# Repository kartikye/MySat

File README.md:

# SASSat
Singapore American School Satellite

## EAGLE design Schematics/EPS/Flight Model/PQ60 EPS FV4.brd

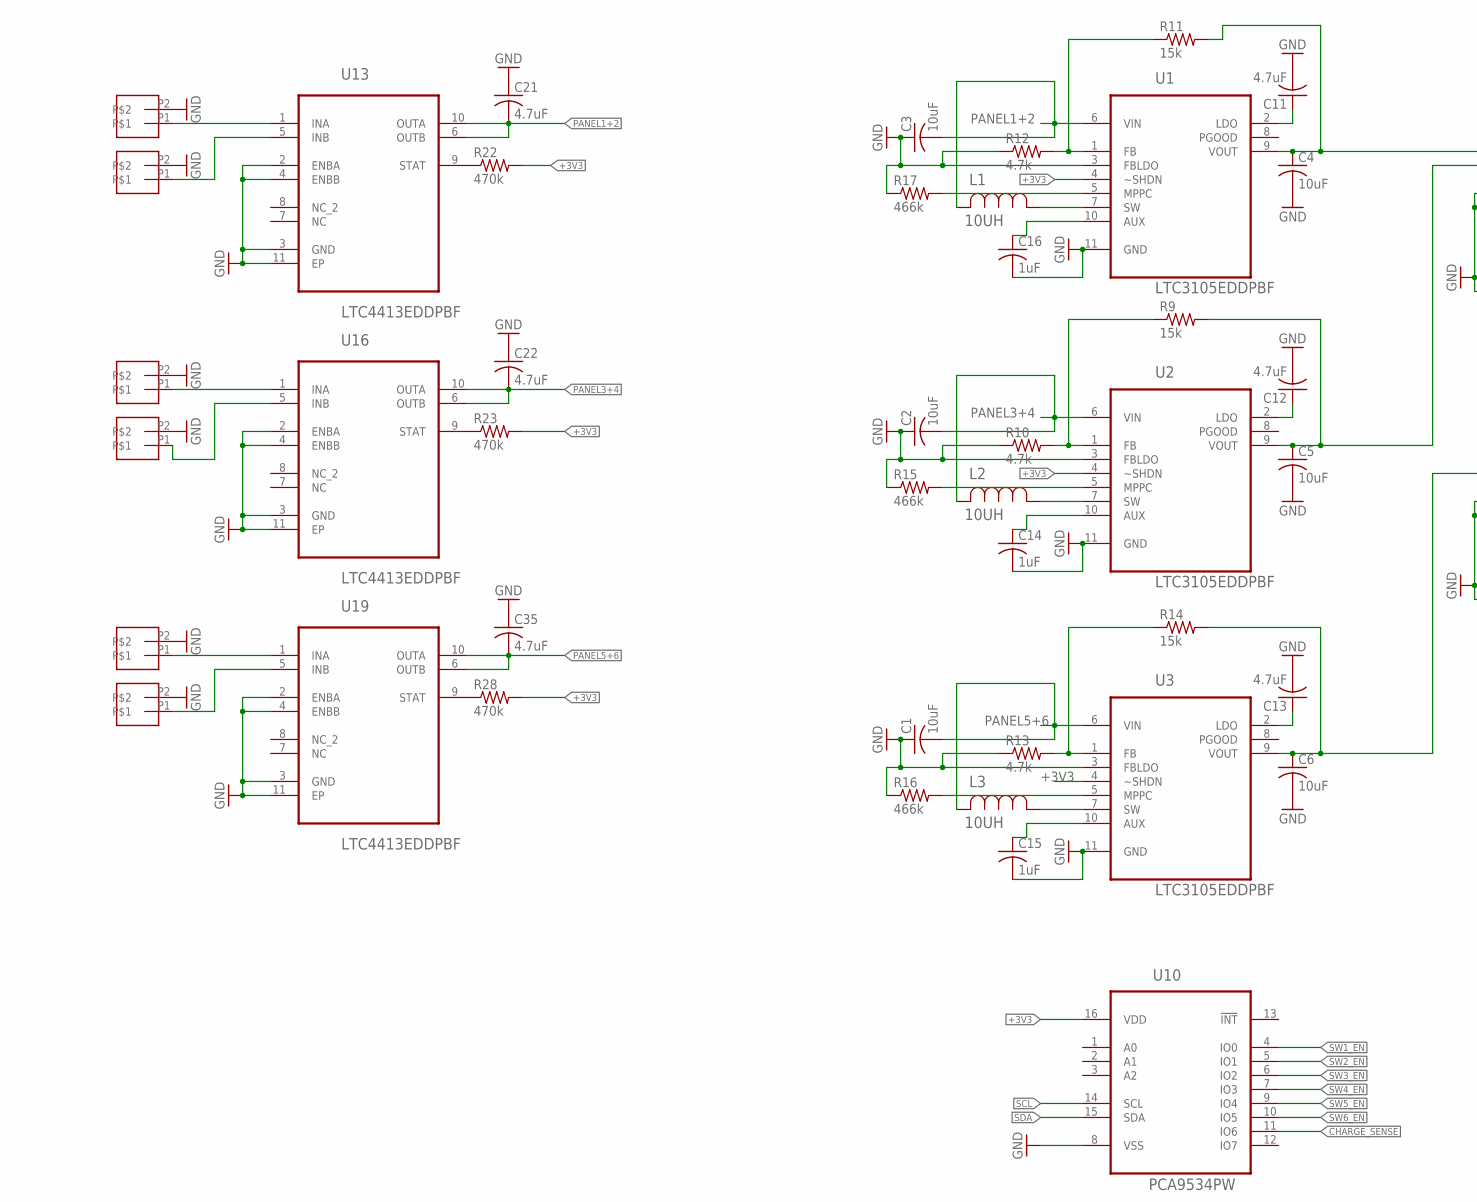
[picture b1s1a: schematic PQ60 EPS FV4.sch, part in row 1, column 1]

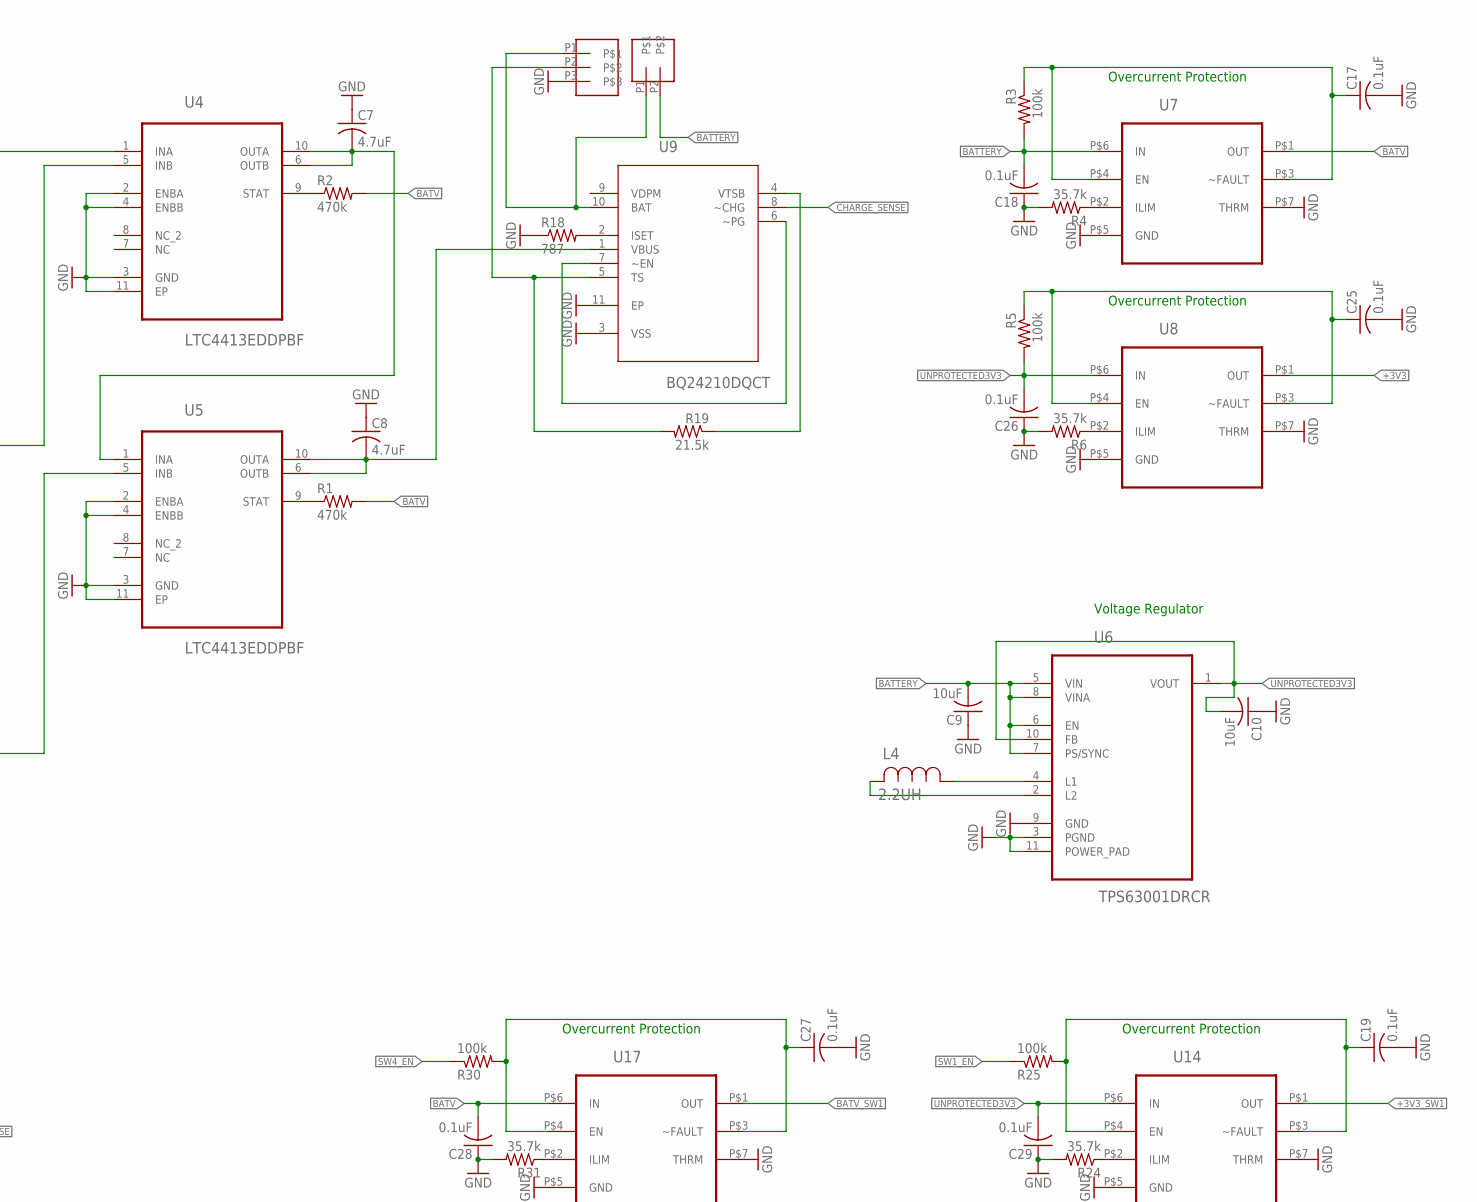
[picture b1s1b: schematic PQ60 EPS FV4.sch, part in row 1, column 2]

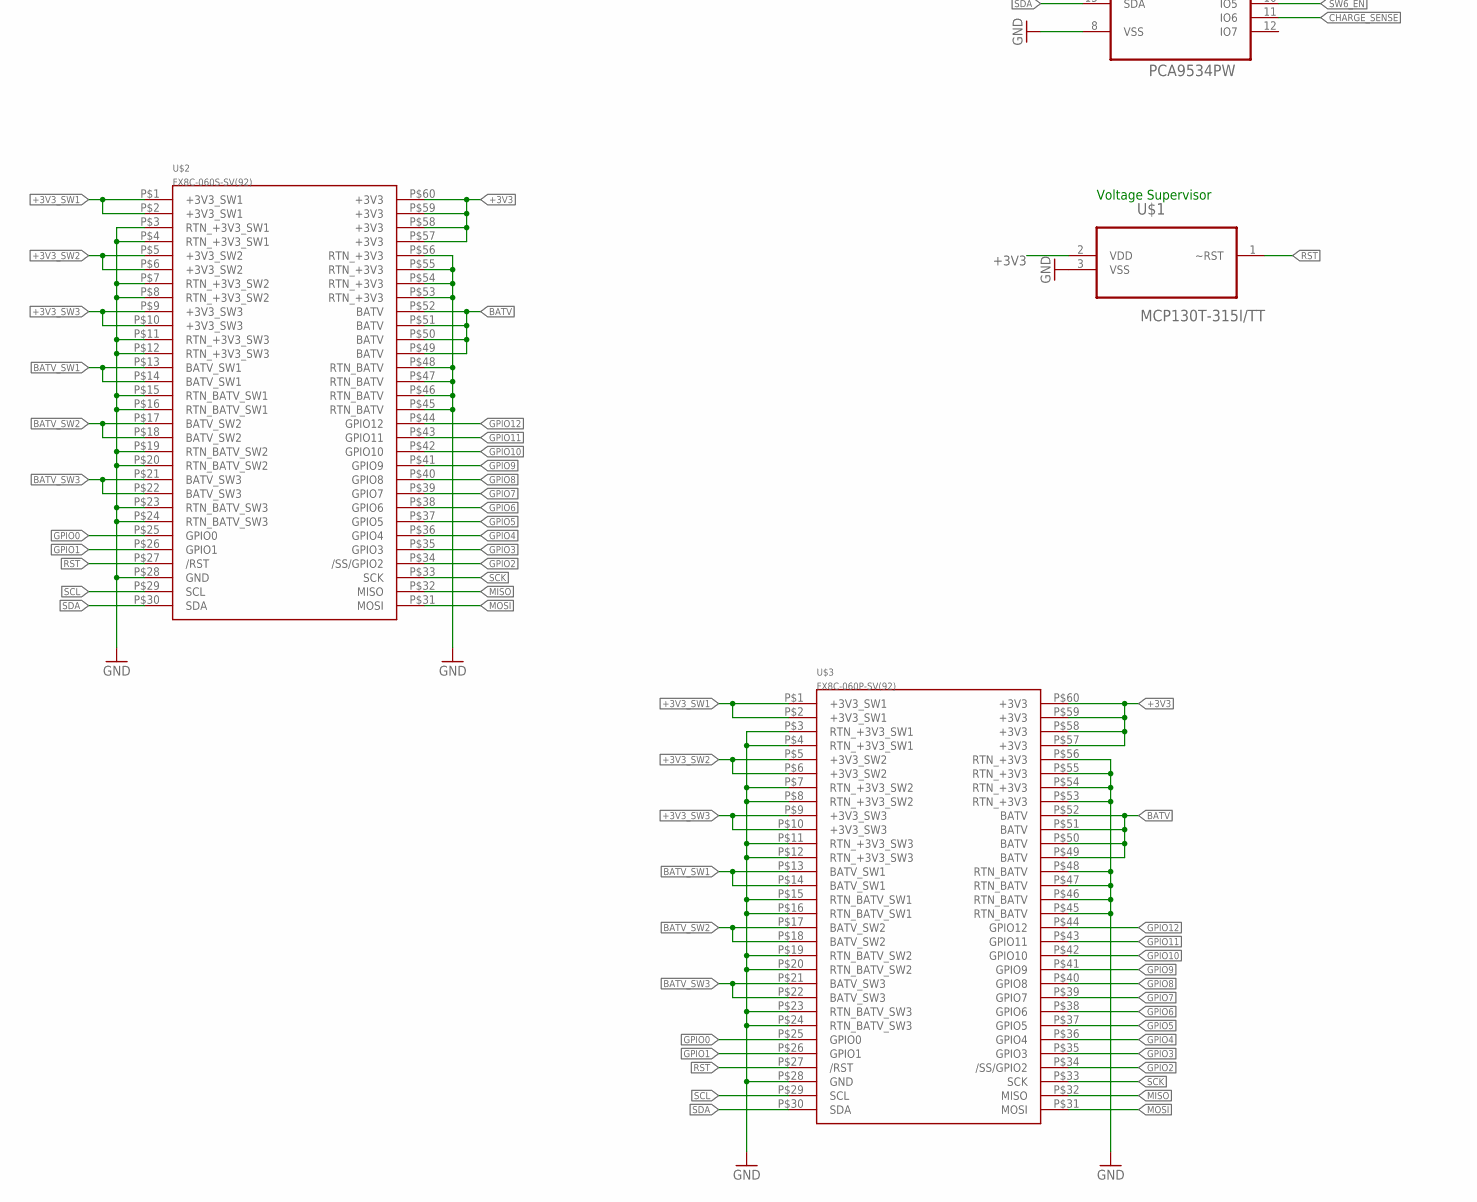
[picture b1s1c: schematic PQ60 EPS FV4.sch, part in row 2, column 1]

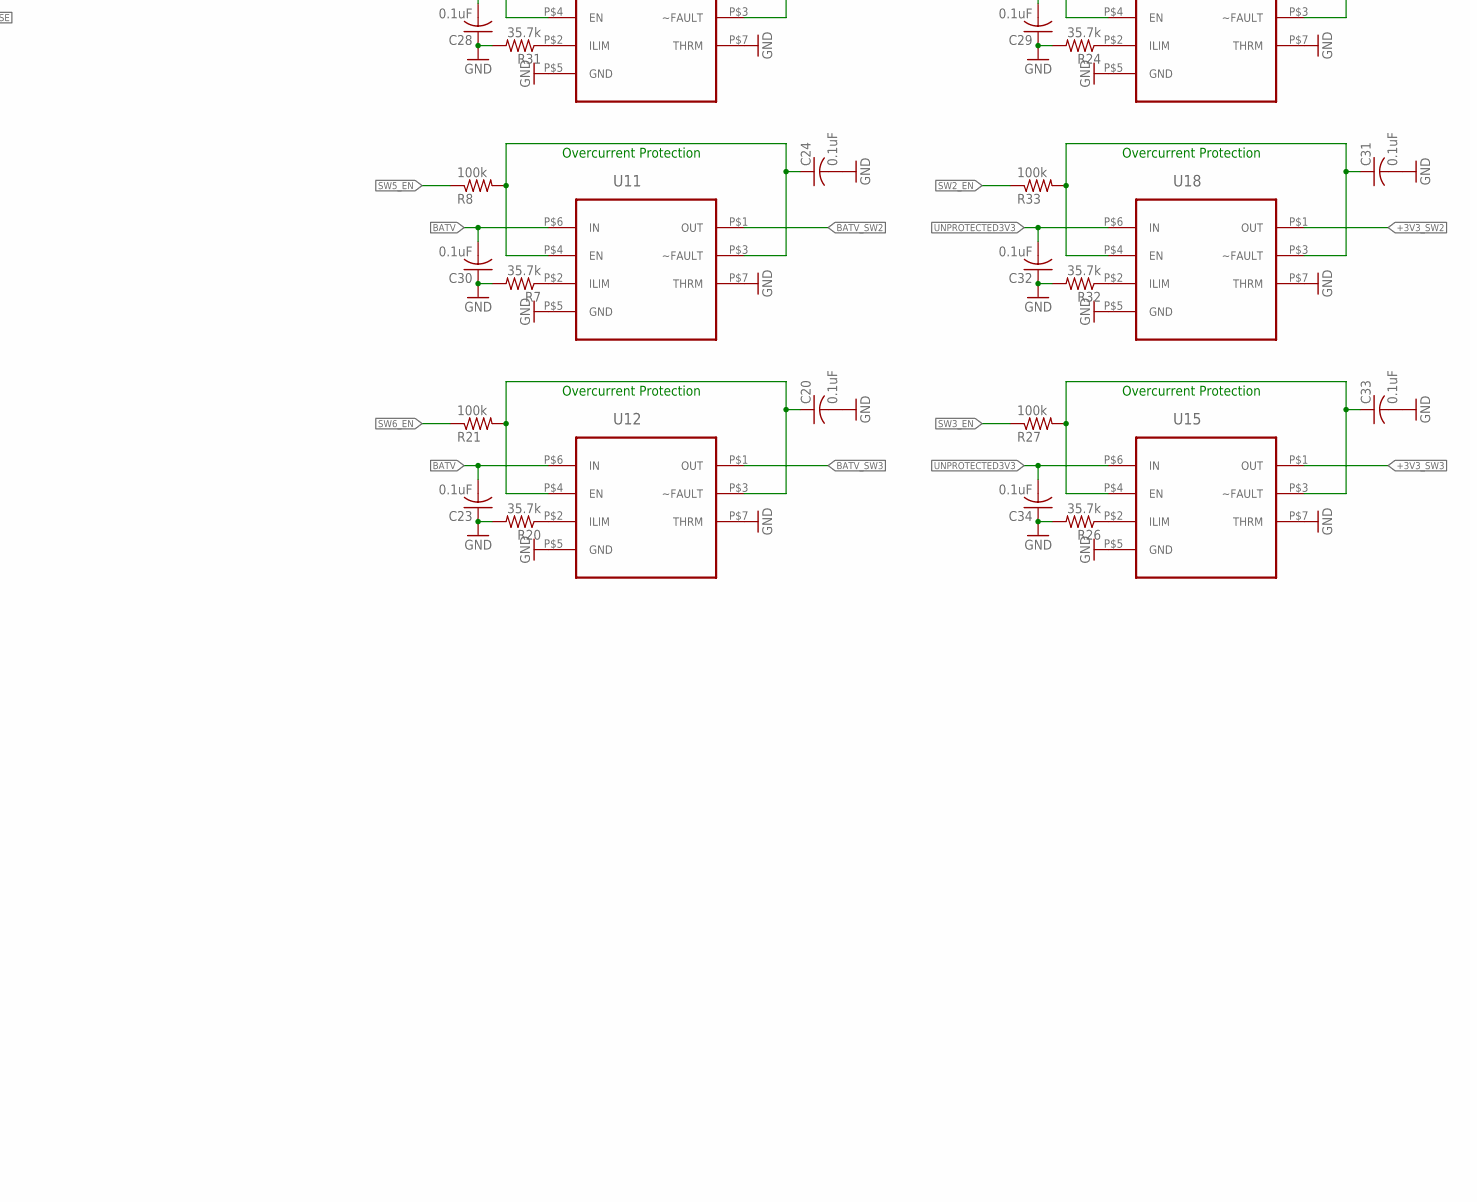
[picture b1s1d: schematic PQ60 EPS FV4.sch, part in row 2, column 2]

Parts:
C1, C2, C3, C4, C5, C6, C9, C10: 10uF; C0805
C7, C8, C11, C12, C13, C21, C22, C35: 4.7uF; C0805
C14, C15, C16: 1uF; C0805
C17, C18, C19, C20, C23, C24, C25, C26, C27, C28, C29, C30, C31, C32, C33, C34: 0.1uF; C0805
L1, L2, L3: 10UH; IND_ELL6XH
L4: 2.2UH; IND_ELL3FU
R1, R2, R22, R23, R28: 470k; R0805
R3, R5, R8, R21, R25, R27, R30, R33: 100k; R0805
R4, R6, R7, R20, R24, R26, R31, R32: 35.7k; R0805
R9, R11, R14: 15k; R0805
R10, R12, R13: 4.7k; R0805
R15, R16, R17: 466k; R0805
R18: 787; R0805
R19: 21.5k; R0805
U1, U2, U3: LTC3105EDDPBF; DFN300X300X80-11N
U4, U5, U13, U16, U19: LTC4413EDDPBF; DFN300X300X80-11N
U6: TPS63001DRCR; SON50P300X300X100-11N
U7, U8, U11, U12, U14, U15, U17, U18: DRV
U9: BQ24210DQCT; SON50P200X300X80-11N
U10: PCA9534PW; SOP65P640X110-16N
U$1: MCP130T-315I/TT; SOT95P237X112-3N
U$2: FX8C-060S-SV(92)
U$3: FX8C-060P-SV(92)
U$4, U$5, U$6, U$7, U$8, U$9, U$10: JST-SH-02
U$11: JST-SH-03

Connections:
!RST: U$1.1 (~RST), U$2.P$27 (/RST), U$3.P$27 (/RST)
+3V3: R22.2, R23.2, R28.2, U1.4 (~SHDN), U2.4 (~SHDN), U3.4 (~SHDN), U8.P$1 (OUT), U10.16 (VDD), U$1.2 (VDD), U$2.P$57 (+3V3), U$2.P$58 (+3V3), U$2.P$59 (+3V3), U$2.P$60 (+3V3), U$3.P$57 (+3V3), U$3.P$58 (+3V3), U$3.P$59 (+3V3), U$3.P$60 (+3V3)
+3V3_SW1: U14.P$1 (OUT), U$2.P$1 (+3V3_SW1), U$2.P$2 (+3V3_SW1), U$3.P$1 (+3V3_SW1), U$3.P$2 (+3V3_SW1)
+3V3_SW2: U18.P$1 (OUT), U$2.P$5 (+3V3_SW2), U$2.P$6 (+3V3_SW2), U$3.P$5 (+3V3_SW2), U$3.P$6 (+3V3_SW2)
+3V3_SW3: U15.P$1 (OUT), U$2.P$9 (+3V3_SW3), U$2.P$10 (+3V3_SW3), U$3.P$9 (+3V3_SW3), U$3.P$10 (+3V3_SW3)
BATTERY: C9.2, C18.2, R3.2, U6.5 (VIN), U6.6 (EN), U6.7 (PS/SYNC), U6.8 (VINA), U7.P$6 (IN), U$10.P2
BATV: C23.2, C28.2, C30.2, R1.2, R2.2, U7.P$1 (OUT), U11.P$6 (IN), U12.P$6 (IN), U17.P$6 (IN), U$2.P$49 (BATV), U$2.P$50 (BATV), U$2.P$51 (BATV), U$2.P$52 (BATV), U$3.P$49 (BATV), U$3.P$50 (BATV), U$3.P$51 (BATV), U$3.P$52 (BATV)
BATV_SW1: U17.P$1 (OUT), U$2.P$13 (BATV_SW1), U$2.P$14 (BATV_SW1), U$3.P$13 (BATV_SW1), U$3.P$14 (BATV_SW1)
BATV_SW2: U11.P$1 (OUT), U$2.P$17 (BATV_SW2), U$2.P$18 (BATV_SW2), U$3.P$17 (BATV_SW2), U$3.P$18 (BATV_SW2)
BATV_SW3: U12.P$1 (OUT), U$2.P$21 (BATV_SW3), U$2.P$22 (BATV_SW3), U$3.P$21 (BATV_SW3), U$3.P$22 (BATV_SW3)
CHARGE_SENSE: U9.8 (~CHG), U10.11 (IO6)
GND: C1.1, C2.1, C3.1, C4.2, C5.2, C6.2, C7.1, C8.1, C9.1, C10.1, C11.2, C12.2, C13.2, C14.2, C15.2, C16.2, C17.2, C18.1, C19.2, C20.2, C21.1, C22.1, C23.1, C24.2, C25.2, C26.1, C27.2, C28.1, C29.1, C30.1, C31.2, C32.1, C33.2, C34.1, C35.1, R4.2, R6.2, R7.2, R10.1, R12.1, R13.1, R15.1, R16.1, R17.1, R18.1, R20.2, R24.2, R26.2, R31.2, R32.2, U1.3 (FBLDO), U1.11 (GND), U2.3 (FBLDO), U2.11 (GND), U3.3 (FBLDO), U3.11 (GND), U4.2 (ENBA), U4.3 (GND), U4.4 (ENBB), U4.11 (EP), U5.2 (ENBA), U5.3 (GND), U5.4 (ENBB), U5.11 (EP), U6.3 (PGND), U6.9 (GND), U6.11 (POWER_PAD), U7.P$5 (GND), U7.P$7 (THRM), U8.P$5 (GND), U8.P$7 (THRM), U9.3 (VSS), U9.11 (EP), U10.8 (VSS), U11.P$5 (GND), U11.P$7 (THRM), U12.P$5 (GND), U12.P$7 (THRM), U13.2 (ENBA), U13.3 (GND), U13.4 (ENBB), U13.11 (EP), U14.P$5 (GND), U14.P$7 (THRM), U15.P$5 (GND), U15.P$7 (THRM), U16.2 (ENBA), U16.3 (GND), U16.4 (ENBB), U16.11 (EP), U17.P$5 (GND), U17.P$7 (THRM), U18.P$5 (GND), U18.P$7 (THRM), U19.2 (ENBA), U19.3 (GND), U19.4 (ENBB), U19.11 (EP), U$1.3 (VSS), U$2.P$3 (RTN_+3V3_SW1), U$2.P$4 (RTN_+3V3_SW1), U$2.P$7 (RTN_+3V3_SW2), U$2.P$8 (RTN_+3V3_SW2), U$2.P$11 (RTN_+3V3_SW3), U$2.P$12 (RTN_+3V3_SW3), U$2.P$15 (RTN_BATV_SW1), U$2.P$16 (RTN_BATV_SW1), U$2.P$19 (RTN_BATV_SW2), U$2.P$20 (RTN_BATV_SW2), U$2.P$23 (RTN_BATV_SW3), U$2.P$24 (RTN_BATV_SW3), U$2.P$28 (GND), U$2.P$45 (RTN_BATV), U$2.P$46 (RTN_BATV), U$2.P$47 (RTN_BATV), U$2.P$48 (RTN_BATV), U$2.P$53 (RTN_+3V3), U$2.P$54 (RTN_+3V3), U$2.P$55 (RTN_+3V3), U$2.P$56 (RTN_+3V3), U$3.P$3 (RTN_+3V3_SW1), U$3.P$4 (RTN_+3V3_SW1), U$3.P$7 (RTN_+3V3_SW2), U$3.P$8 (RTN_+3V3_SW2), U$3.P$11 (RTN_+3V3_SW3), U$3.P$12 (RTN_+3V3_SW3), U$3.P$15 (RTN_BATV_SW1), U$3.P$16 (RTN_BATV_SW1), U$3.P$19 (RTN_BATV_SW2), U$3.P$20 (RTN_BATV_SW2), U$3.P$23 (RTN_BATV_SW3), U$3.P$24 (RTN_BATV_SW3), U$3.P$28 (GND), U$3.P$45 (RTN_BATV), U$3.P$46 (RTN_BATV), U$3.P$47 (RTN_BATV), U$3.P$48 (RTN_BATV), U$3.P$53 (RTN_+3V3), U$3.P$54 (RTN_+3V3), U$3.P$55 (RTN_+3V3), U$3.P$56 (RTN_+3V3), U$4.P2, U$5.P2, U$6.P2, U$7.P2, U$8.P2, U$9.P2, U$11.P3
GPIO0: U$2.P$25 (GPIO0), U$3.P$25 (GPIO0)
GPIO1: U$2.P$26 (GPIO1), U$3.P$26 (GPIO1)
GPIO2: U$2.P$34 (/SS/GPIO2), U$3.P$34 (/SS/GPIO2)
GPIO3: U$2.P$35 (GPIO3), U$3.P$35 (GPIO3)
GPIO4: U$2.P$36 (GPIO4), U$3.P$36 (GPIO4)
GPIO5: U$2.P$37 (GPIO5), U$3.P$37 (GPIO5)
GPIO6: U$2.P$38 (GPIO6), U$3.P$38 (GPIO6)
GPIO7: U$2.P$39 (GPIO7), U$3.P$39 (GPIO7)
GPIO8: U$2.P$40 (GPIO8), U$3.P$40 (GPIO8)
GPIO9: U$2.P$41 (GPIO9), U$3.P$41 (GPIO9)
GPIO10: U$2.P$42 (GPIO10), U$3.P$42 (GPIO10)
GPIO11: U$2.P$43 (GPIO11), U$3.P$43 (GPIO11)
GPIO12: U$2.P$44 (GPIO12), U$3.P$44 (GPIO12)
MISO: U$2.P$32 (MISO), U$3.P$32 (MISO)
MOSI: U$2.P$31 (MOSI), U$3.P$31 (MOSI)
unnamed: L2.1, U2.7 (SW)
unnamed: L3.1, U3.7 (SW)
unnamed: L1.1, U1.7 (SW)
unnamed: L4.1, U6.4 (L1)
unnamed: C4.1, R11.2, U1.9 (VOUT), U4.1 (INA)
unnamed: C5.1, R9.2, U2.9 (VOUT), U4.5 (INB)
unnamed: C6.1, R14.2, U3.9 (VOUT), U5.5 (INB)
unnamed: C17.1, R3.1, U7.P$3 (~FAULT), U7.P$4 (EN)
unnamed: C7.2, U4.6 (OUTB), U4.10 (OUTA), U5.1 (INA)
unnamed: R1.1, U5.9 (STAT)
unnamed: R2.1, U4.9 (STAT)
unnamed: L4.2, U6.2 (L2)
unnamed: R4.1, U7.P$2 (ILIM)
unnamed: R6.1, U8.P$2 (ILIM)
unnamed: C25.1, R5.1, U8.P$3 (~FAULT), U8.P$4 (EN)
unnamed: R7.1, U11.P$2 (ILIM)
unnamed: C24.1, R8.2, U11.P$3 (~FAULT), U11.P$4 (EN)
unnamed: R13.2, R14.1, U3.1 (FB)
unnamed: C11.1, U1.2 (LDO)
unnamed: C12.1, U2.2 (LDO)
unnamed: C13.1, U3.2 (LDO)
unnamed: C14.1, U2.10 (AUX)
unnamed: C15.1, U3.10 (AUX)
unnamed: C16.1, U1.10 (AUX)
unnamed: R11.1, R12.2, U1.1 (FB)
unnamed: R9.1, R10.2, U2.1 (FB)
unnamed: R31.1, U17.P$2 (ILIM)
unnamed: R15.2, U2.5 (MPPC)
unnamed: R16.2, U3.5 (MPPC)
unnamed: R17.2, U1.5 (MPPC)
unnamed: C8.2, U5.6 (OUTB), U5.10 (OUTA), U9.1 (VBUS)
unnamed: U9.6 (~PG), U9.7 (~EN)
unnamed: R18.2, U9.2 (ISET)
unnamed: U9.10 (BAT), U$10.P1, U$11.P1
unnamed: R19.2, U9.5 (TS), U$11.P2
unnamed: R19.1, U9.4 (VTSB)
unnamed: C27.1, R30.2, U17.P$3 (~FAULT), U17.P$4 (EN)
unnamed: R20.1, U12.P$2 (ILIM)
unnamed: C20.1, R21.2, U12.P$3 (~FAULT), U12.P$4 (EN)
unnamed: R23.1, U16.9 (STAT)
unnamed: R28.1, U19.9 (STAT)
unnamed: R24.1, U14.P$2 (ILIM)
unnamed: C19.1, R25.2, U14.P$3 (~FAULT), U14.P$4 (EN)
unnamed: R26.1, U15.P$2 (ILIM)
unnamed: C33.1, R27.2, U15.P$3 (~FAULT), U15.P$4 (EN)
unnamed: U13.1 (INA), U$5.P1
unnamed: U13.5 (INB), U$4.P1
unnamed: R32.1, U18.P$2 (ILIM)
unnamed: C31.1, R33.2, U18.P$3 (~FAULT), U18.P$4 (EN)
unnamed: U16.1 (INA), U$6.P1
unnamed: U16.5 (INB), U$7.P1
unnamed: U19.1 (INA), U$9.P1
unnamed: U19.5 (INB), U$8.P1
unnamed: R22.1, U13.9 (STAT)
PANEL1+2: C3.2, C21.2, L1.2, U1.6 (VIN), U13.6 (OUTB), U13.10 (OUTA)
PANEL3+4: C2.2, C22.2, L2.2, U2.6 (VIN), U16.6 (OUTB), U16.10 (OUTA)
PANEL5+6: C1.2, C35.2, L3.2, U3.6 (VIN), U19.6 (OUTB), U19.10 (OUTA)
SCK: U$2.P$33 (SCK), U$3.P$33 (SCK)
SCL: U10.14 (SCL), U$2.P$29 (SCL), U$3.P$29 (SCL)
SDA: U10.15 (SDA), U$2.P$30 (SDA), U$3.P$30 (SDA)
SW1_EN: R25.1, U10.4 (IO0)
SW2_EN: R33.1, U10.5 (IO1)
SW3_EN: R27.1, U10.6 (IO2)
SW4_EN: R30.1, U10.7 (IO3)
SW5_EN: R8.1, U10.9 (IO4)
SW6_EN: R21.1, U10.10 (IO5)
UNPROTECTED3V3: C10.2, C26.2, C29.2, C32.2, C34.2, R5.2, U6.1 (VOUT), U6.10 (FB), U8.P$6 (IN), U14.P$6 (IN), U15.P$6 (IN), U18.P$6 (IN)

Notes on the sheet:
Voltage Regulator
Voltage Supervisor
Overcurrent Protection

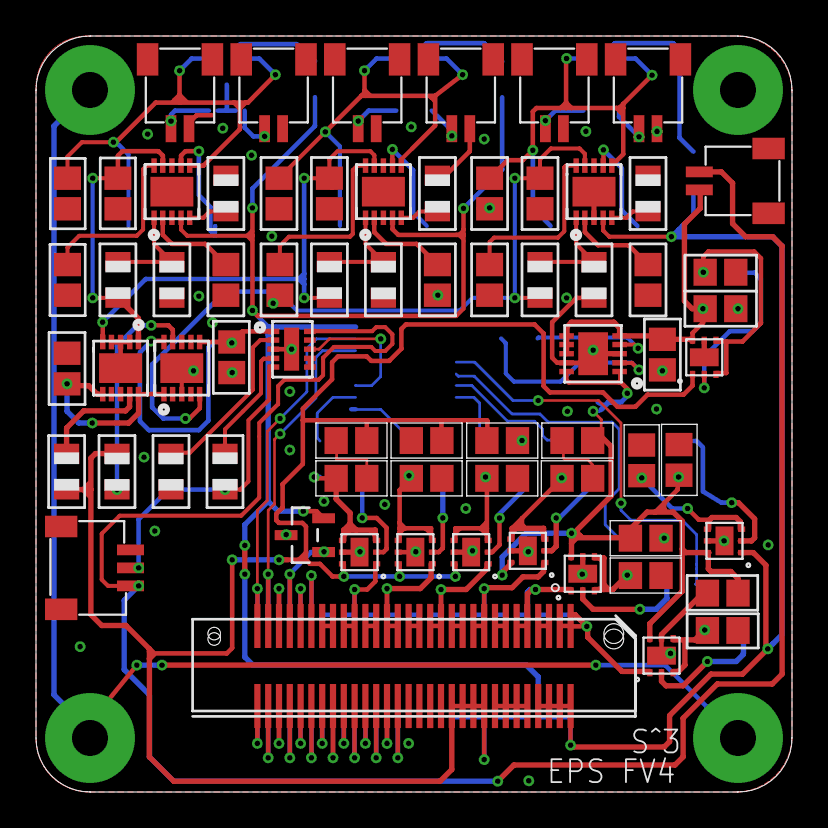
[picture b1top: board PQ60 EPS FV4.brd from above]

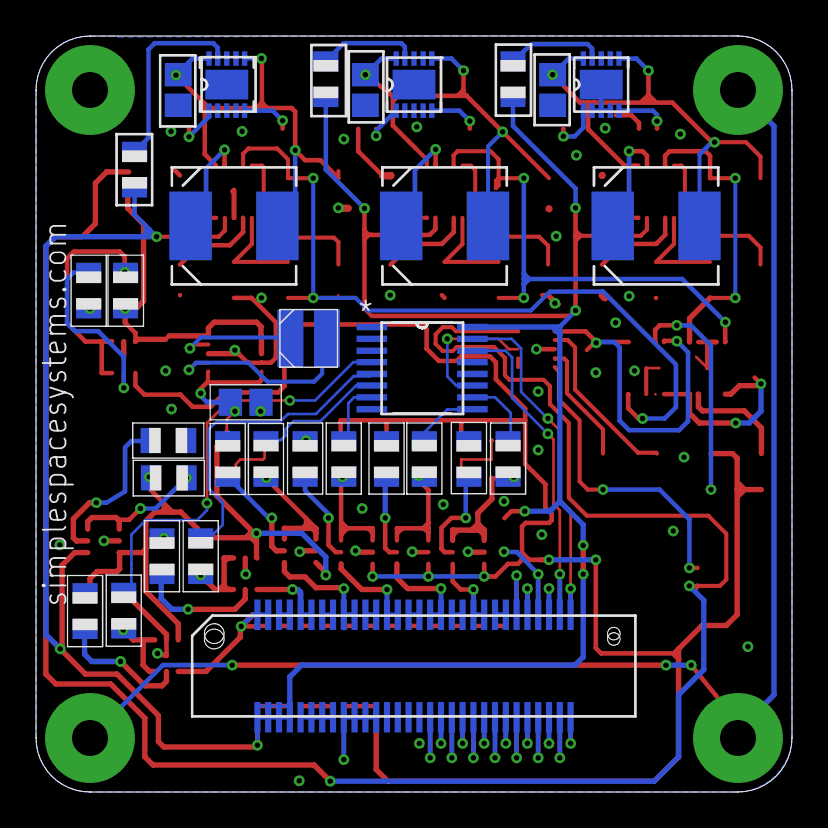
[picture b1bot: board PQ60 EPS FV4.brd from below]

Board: 2 copper layers, 42.0 x 42.0 mm, 101 parts (32 on the bottom side), 94 nets.

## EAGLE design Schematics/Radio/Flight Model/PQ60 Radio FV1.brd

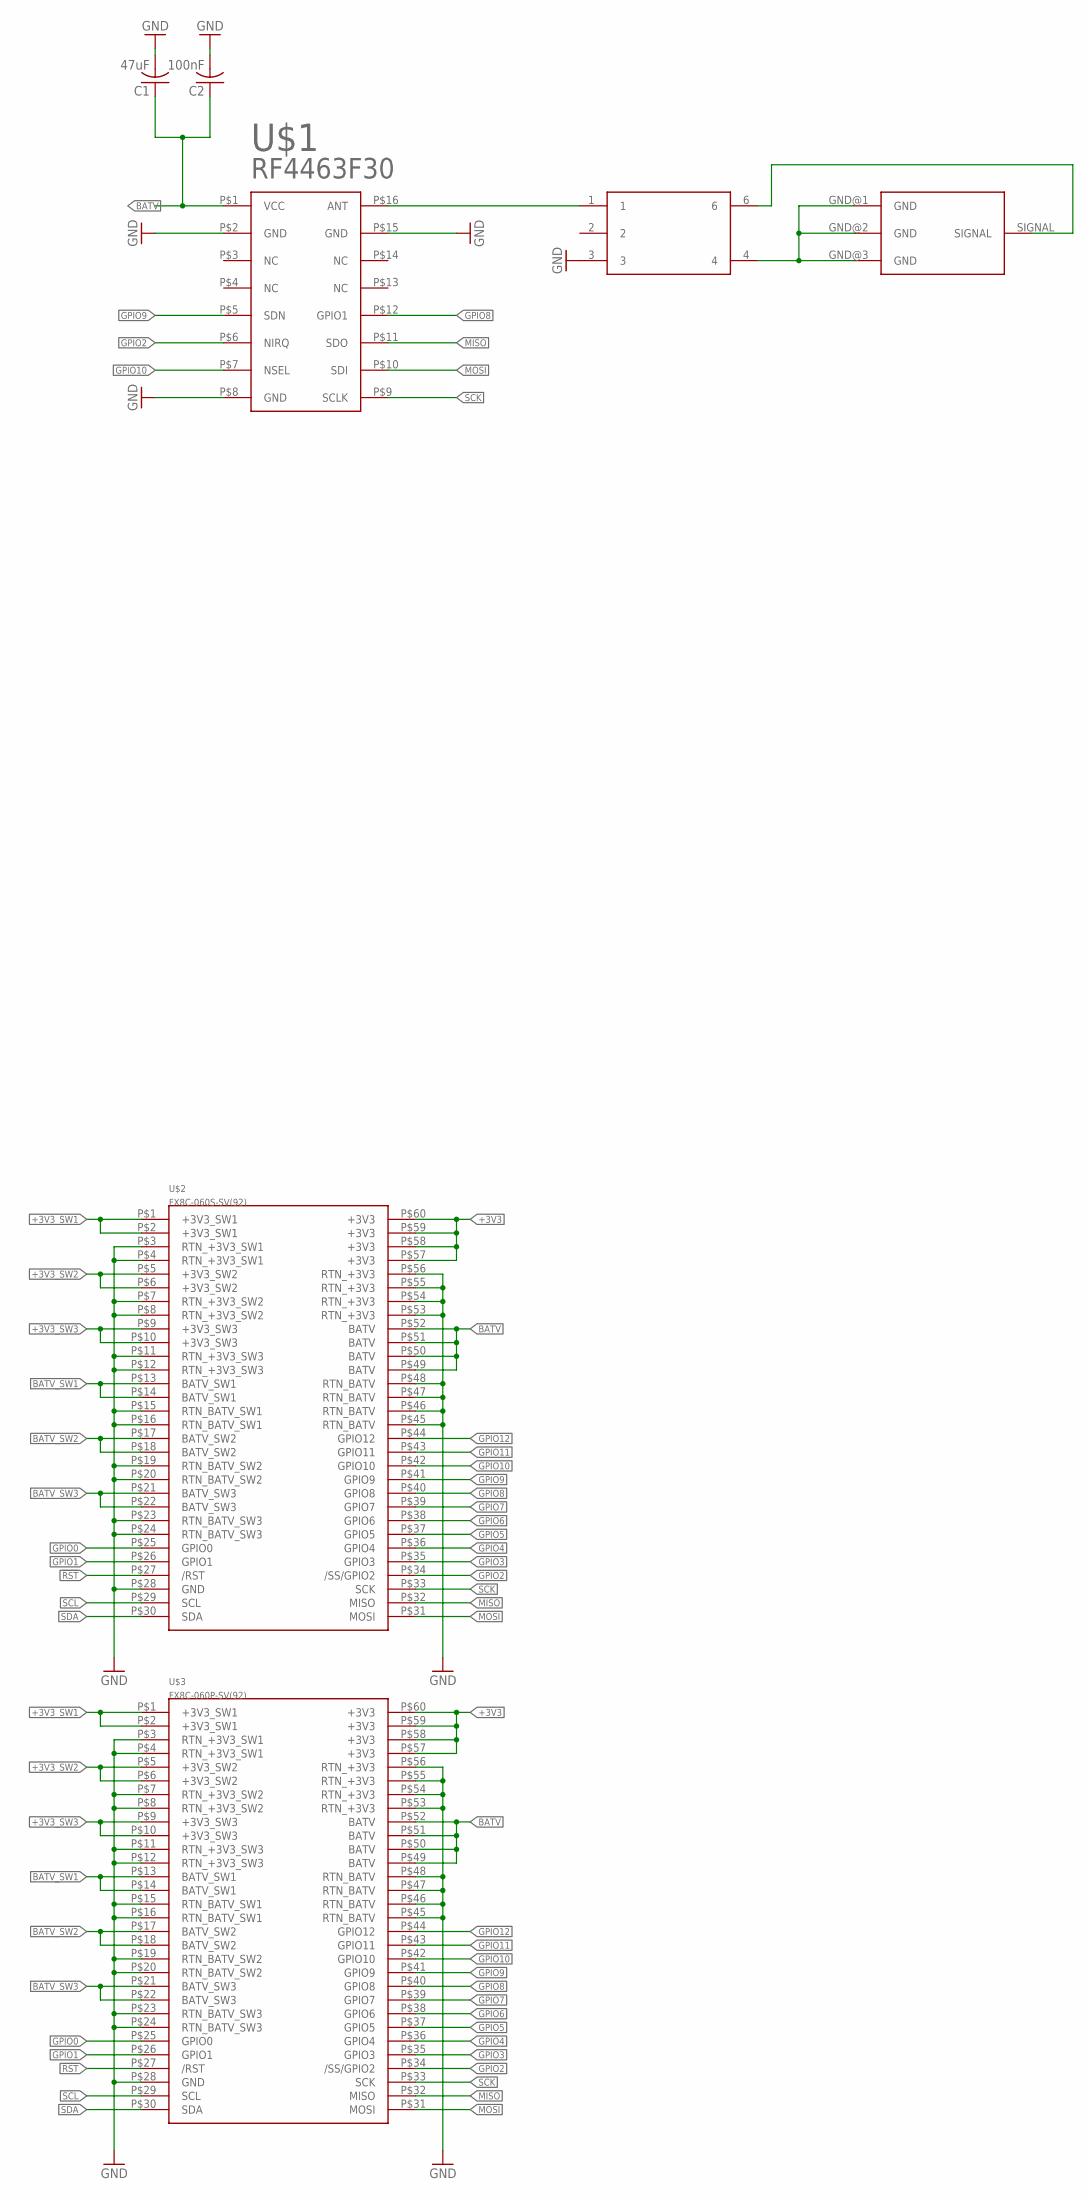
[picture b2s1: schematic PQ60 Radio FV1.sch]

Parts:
C1: 47uF; C0805
C2: 100nF; C0805
CX2156NL: CX2156NL
U$1: RF4463F30
U$2: FX8C-060S-SV(92)
U$3: FX8C-060P-SV(92)
U$4: MICRO-SMA

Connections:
!RST: U$2.P$27 (/RST), U$3.P$27 (/RST)
+3V3: U$2.P$57 (+3V3), U$2.P$58 (+3V3), U$2.P$59 (+3V3), U$2.P$60 (+3V3), U$3.P$57 (+3V3), U$3.P$58 (+3V3), U$3.P$59 (+3V3), U$3.P$60 (+3V3)
+3V3_SW1: U$2.P$1 (+3V3_SW1), U$2.P$2 (+3V3_SW1), U$3.P$1 (+3V3_SW1), U$3.P$2 (+3V3_SW1)
+3V3_SW2: U$2.P$5 (+3V3_SW2), U$2.P$6 (+3V3_SW2), U$3.P$5 (+3V3_SW2), U$3.P$6 (+3V3_SW2)
+3V3_SW3: U$2.P$9 (+3V3_SW3), U$2.P$10 (+3V3_SW3), U$3.P$9 (+3V3_SW3), U$3.P$10 (+3V3_SW3)
BATV: C1.1, C2.1, U$1.P$1 (VCC), U$2.P$49 (BATV), U$2.P$50 (BATV), U$2.P$51 (BATV), U$2.P$52 (BATV), U$3.P$49 (BATV), U$3.P$50 (BATV), U$3.P$51 (BATV), U$3.P$52 (BATV)
BATV_SW1: U$2.P$13 (BATV_SW1), U$2.P$14 (BATV_SW1), U$3.P$13 (BATV_SW1), U$3.P$14 (BATV_SW1)
BATV_SW2: U$2.P$17 (BATV_SW2), U$2.P$18 (BATV_SW2), U$3.P$17 (BATV_SW2), U$3.P$18 (BATV_SW2)
BATV_SW3: U$2.P$21 (BATV_SW3), U$2.P$22 (BATV_SW3), U$3.P$21 (BATV_SW3), U$3.P$22 (BATV_SW3)
GND: C1.2, C2.2, CX2156NL.3, U$1.P$2 (GND), U$1.P$8 (GND), U$1.P$15 (GND), U$2.P$3 (RTN_+3V3_SW1), U$2.P$4 (RTN_+3V3_SW1), U$2.P$7 (RTN_+3V3_SW2), U$2.P$8 (RTN_+3V3_SW2), U$2.P$11 (RTN_+3V3_SW3), U$2.P$12 (RTN_+3V3_SW3), U$2.P$15 (RTN_BATV_SW1), U$2.P$16 (RTN_BATV_SW1), U$2.P$19 (RTN_BATV_SW2), U$2.P$20 (RTN_BATV_SW2), U$2.P$23 (RTN_BATV_SW3), U$2.P$24 (RTN_BATV_SW3), U$2.P$28 (GND), U$2.P$45 (RTN_BATV), U$2.P$46 (RTN_BATV), U$2.P$47 (RTN_BATV), U$2.P$48 (RTN_BATV), U$2.P$53 (RTN_+3V3), U$2.P$54 (RTN_+3V3), U$2.P$55 (RTN_+3V3), U$2.P$56 (RTN_+3V3), U$3.P$3 (RTN_+3V3_SW1), U$3.P$4 (RTN_+3V3_SW1), U$3.P$7 (RTN_+3V3_SW2), U$3.P$8 (RTN_+3V3_SW2), U$3.P$11 (RTN_+3V3_SW3), U$3.P$12 (RTN_+3V3_SW3), U$3.P$15 (RTN_BATV_SW1), U$3.P$16 (RTN_BATV_SW1), U$3.P$19 (RTN_BATV_SW2), U$3.P$20 (RTN_BATV_SW2), U$3.P$23 (RTN_BATV_SW3), U$3.P$24 (RTN_BATV_SW3), U$3.P$28 (GND), U$3.P$45 (RTN_BATV), U$3.P$46 (RTN_BATV), U$3.P$47 (RTN_BATV), U$3.P$48 (RTN_BATV), U$3.P$53 (RTN_+3V3), U$3.P$54 (RTN_+3V3), U$3.P$55 (RTN_+3V3), U$3.P$56 (RTN_+3V3)
GPIO0: U$2.P$25 (GPIO0), U$3.P$25 (GPIO0)
GPIO1: U$2.P$26 (GPIO1), U$3.P$26 (GPIO1)
GPIO2: U$1.P$6 (NIRQ), U$2.P$34 (/SS/GPIO2), U$3.P$34 (/SS/GPIO2)
GPIO3: U$2.P$35 (GPIO3), U$3.P$35 (GPIO3)
GPIO4: U$2.P$36 (GPIO4), U$3.P$36 (GPIO4)
GPIO5: U$2.P$37 (GPIO5), U$3.P$37 (GPIO5)
GPIO6: U$2.P$38 (GPIO6), U$3.P$38 (GPIO6)
GPIO7: U$2.P$39 (GPIO7), U$3.P$39 (GPIO7)
GPIO8: U$1.P$12 (GPIO1), U$2.P$40 (GPIO8), U$3.P$40 (GPIO8)
GPIO9: U$1.P$5 (SDN), U$2.P$41 (GPIO9), U$3.P$41 (GPIO9)
GPIO10: U$1.P$7 (NSEL), U$2.P$42 (GPIO10), U$3.P$42 (GPIO10)
GPIO11: U$2.P$43 (GPIO11), U$3.P$43 (GPIO11)
GPIO12: U$2.P$44 (GPIO12), U$3.P$44 (GPIO12)
MISO: U$1.P$11 (SDO), U$2.P$32 (MISO), U$3.P$32 (MISO)
MOSI: U$1.P$10 (SDI), U$2.P$31 (MOSI), U$3.P$31 (MOSI)
unnamed: CX2156NL.1, U$1.P$16 (ANT)
unnamed: CX2156NL.6, U$4.SIGNAL
unnamed: CX2156NL.4, U$4.GND@1 (GND), U$4.GND@2 (GND), U$4.GND@3 (GND)
SCK: U$1.P$9 (SCLK), U$2.P$33 (SCK), U$3.P$33 (SCK)
SCL: U$2.P$29 (SCL), U$3.P$29 (SCL)
SDA: U$2.P$30 (SDA), U$3.P$30 (SDA)

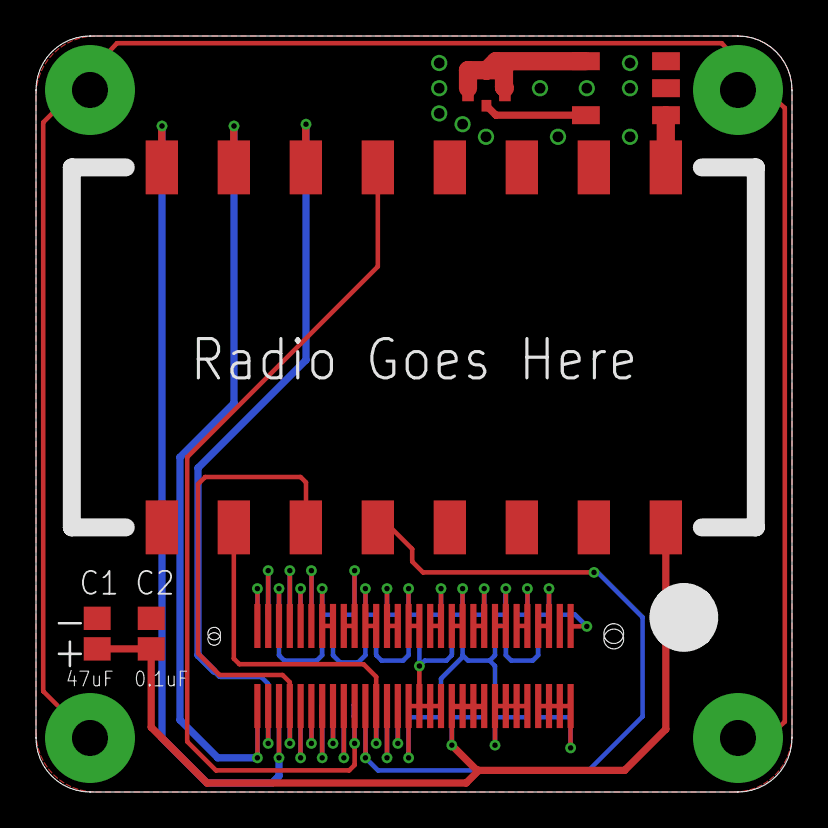
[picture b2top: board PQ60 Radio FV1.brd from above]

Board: 2 copper layers, 42.0 x 42.0 mm, 7 parts (1 on the bottom side), 31 nets.

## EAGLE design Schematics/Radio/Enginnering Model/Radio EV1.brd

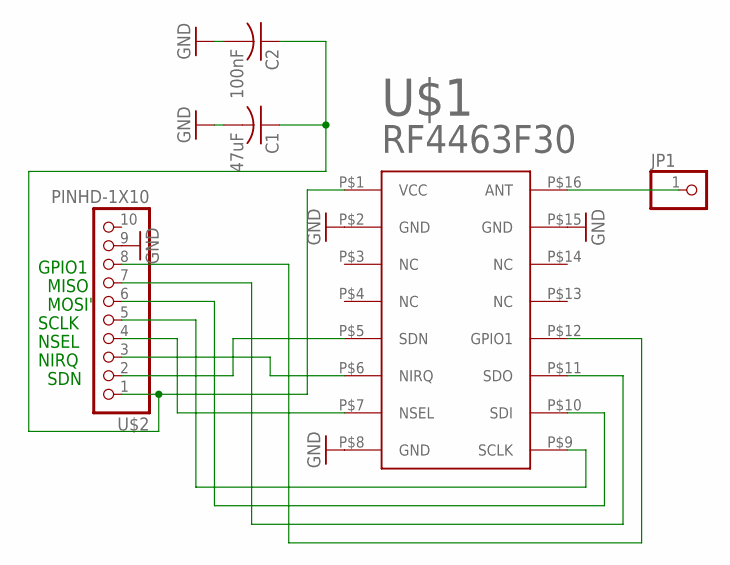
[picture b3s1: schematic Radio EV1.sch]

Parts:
C1: 47uF; C0805
C2: 100nF; C0805
JP1: PINHD-1X1CB; 1X01-CLEANBIG
U$1: RF4463F30
U$2: PINHD-1X10; 1X10-BIG

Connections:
GND: C1.2, C2.2, U$1.P$2 (GND), U$1.P$8 (GND), U$1.P$15 (GND), U$2.9
GPIO1: U$1.P$12 (GPIO1), U$2.8
unnamed: JP1.1, U$1.P$16 (ANT)
NIRQ: U$1.P$6 (NIRQ), U$2.3
NSEL: U$1.P$7 (NSEL), U$2.4
SCLK: U$1.P$9 (SCLK), U$2.5
SDI: U$1.P$10 (SDI), U$2.6
SDN: U$1.P$5 (SDN), U$2.2
SDO: U$1.P$11 (SDO), U$2.7
VCC: C1.1, C2.1, U$1.P$1 (VCC), U$2.1

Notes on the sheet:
SDN
NIRQ
NSEL
SCLK
MOSI'
MISO
GPIO1

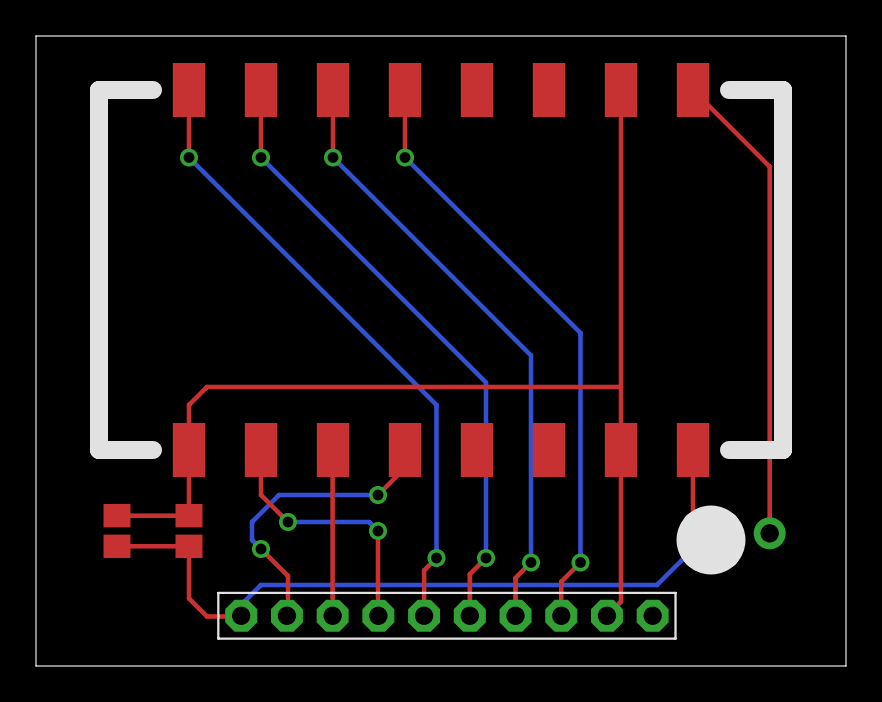
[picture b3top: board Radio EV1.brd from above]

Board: 2 copper layers, 45.0 x 35.0 mm, 5 parts (0 on the bottom side), 10 nets.

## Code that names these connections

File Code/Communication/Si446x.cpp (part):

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void Si446x::init() {
  
  pinMode(VCXO_ENABLE_PIN, OUTPUT);
  pinMode(GPIO0_PIN, OUTPUT);
  
  digitalWrite(VCXO_ENABLE_PIN,HIGH);
  //Serial.println("VCXO is enabled"); 
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
  Serial.println("Radio ready");
 
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  SendCmdReceiveAnswer(6, 8, gpio_pin_cfg_command);

  Serial.println("LEDs should be switched off at this point");
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void Si446x::setModem()
{
  // Set to CW mode
  //Serial.println("Setting modem into direct asynchronous 2FSK mode using GPIO0");  
  char set_modem_mod_type_command[] = {0x11, 0x20, 0x01, 0x00, 0b10001010};
  SendCmdReceiveAnswer(5, 1, set_modem_mod_type_command);
  
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  
  digitalWrite(VCXO_ENABLE_PIN, HIGH);
  init();
  // turn on the blue LED (GPIO2) to indicate TX
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  SendCmdReceiveAnswer(8, 1, gpio_pin_cfg_command2);

  start_tx(1);
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{
  stop_tx();
  si446x_powerlevel = 0;
  // turn off the blue LED (GPIO2)
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  SendCmdReceiveAnswer(8, 1, gpio_pin_cfg_command0);

  digitalWrite(RADIO_SDN_PIN, HIGH);  // active high = shutdown
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void Si446x::setHighTone()
{
  //analogWrite(VCXO_CONTROL_PIN, 131);
  digitalWrite(GPIO0_PIN, HIGH);
}

void Si446x::setLowTone()
{
  //analogWrite(VCXO_CONTROL_PIN, 124);
  digitalWrite(GPIO0_PIN, LOW);
}


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
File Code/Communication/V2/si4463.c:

#include "si4463.h"
#include "si4463_config.h"
#include <avr/io.h>
#include <avr/interrupt.h>
#include <util/crc16.h>
#include <SPI.h>
#include <Wire.h>
#include <avr/power.h>
#include <avr/sleep.h>
#include <math.h>
//API Codes

#define NOP 							0x00 
#define PART_INFO                       0x01
#define FUNC_INFO                       0x10
#define SET_PROPERTY                    0x11 
#define GET_PROPERTY                    0x12 
#define GPIO_PIN_CFG                    0x13
#define GET_ADC_READING                 0x14 
#define FIFO_INFO                       0x15
#define PACKET_INFO                     0x16
#define IRCAL                           0x17 
#define PROTOCOL_CFG                    0x18 
#define GET_INT_STATUS                  0x20
#define GET_PH_STATUS                   0x21
#define GET_MODEM_STATUS                0x22
#define GET_CHIP_STATUS                 0x23
#define START_TX                        0x31 
#define START_RX                        0x32 
#define REQUEST_DEVICE_STAT             0x33
#define CHANGE_STATE                    0x34 
#define READ_CMD_BUFF                   0x44 
#define FRR_A_READ                      0x50
#define FRR_B_READ                      0x51 
#define FRR_C_READ                      0x53 
#define FRR_D_READ                      0x57 
#define WRITE_TX_FIFO                   0x66 
#define READ_RX_FIFO                    0x77 
#define START_MFSK                      0x35 
#define RX_HOP                          0x36 

//config

#define CALLSIGN "D-2"                  //Callsign
#define SEC_CALLSIGN "AF5LI"            //Secondary Callsign which is sent but not included in the package
#define ASCII 7                         //ASCII 7 or 8
#define STOPBITS 2                      //Either 1 or 2
#define TXDELAY 25                      //Transmit-Delay in bits
#define RTTY_BAUD 50                    //Baud rate (600 max)
#define RADIO_FREQUENCY 435.300         //Transmit frequency in MHz (119 - 1050 Mhz)
#define RTTY_SHIFT 440                  //RTTY shift in Hz (varies, differs also on 2m and 70cm)
                                        //490 = 450 Hz @ 434.500 MHz
                                        //440 = 425 Hz @ 145.300 MHz
#define POWER_LEVEL 20

const unsigned char RF_MODEM_CLKGEN_BAND_1_data[] = 		{RF_MODEM_CLKGEN_BAND_1};
const unsigned char RF_FREQ_CONTROL_INTE_8_data[] = 		{RF_FREQ_CONTROL_INTE_8};
const unsigned char RF_POWER_UP_data[] = 			   		{ RF_POWER_UP};
const unsigned char RF_GPIO_PIN_CFG_data[] = 			   	{ RF_GPIO_PIN_CFG}; 
const unsigned char RF_GLOBAL_XO_TUNE_1_data[] = 		   	{ RF_GLOBAL_XO_TUNE_1};
const unsigned char RF_GLOBAL_CONFIG_1_data[] = 		   	{ RF_GLOBAL_CONFIG_1}; 
const unsigned char RF_FRR_CTL_A_MODE_4_data[] = 		   	{ RF_FRR_CTL_A_MODE_4};
const unsigned char RF_PREAMBLE_TX_LENGTH_9_data[] = 		{ RF_PREAMBLE_TX_LENGTH_9};
const unsigned char RF_SYNC_CONFIG_5_data[] = 		 	   	{ RF_SYNC_CONFIG_5};
const unsigned char RF_PKT_CRC_CONFIG_1_data[] = 		   	{ RF_PKT_CRC_CONFIG_1};
const unsigned char RF_PKT_CONFIG1_1_data[] = 			   	{ RF_PKT_CONFIG1_1};
const unsigned char RF_PKT_LEN_3_data[] = 			   		{ RF_PKT_LEN_3};
const unsigned char RF_PKT_FIELD_1_LENGTH_12_8_12_data[] =	{ RF_PKT_FIELD_1_LENGTH_12_8_12};
const unsigned char RF_PKT_FIELD_4_LENGTH_12_8_8_data[] = 	{ RF_PKT_FIELD_4_LENGTH_12_8_8};
const unsigned char RF_MODEM_FREQ_DEV_0_1_data[] = 		   	{ RF_MODEM_FREQ_DEV_0_1};
const unsigned char RF_MODEM_AGC_CONTROL_1_data[] = 		{ RF_MODEM_AGC_CONTROL_1};
const unsigned char RF_MATCH_VALUE_1_12_data[] =            { RF_MATCH_VALUE_1_12};
const unsigned char RF_MODEM_RSSI_COMP_1_data[] = 			{ RF_MODEM_RSSI_COMP_1};
const unsigned char RF_MODEM_MOD_TYPE_12_data[]=			{RF_MODEM_MOD_TYPE_12};
const unsigned char RF_MODEM_TX_RAMP_DELAY_8_data[]=				{RF_MODEM_TX_RAMP_DELAY_8};
const unsigned char RF_MODEM_BCR_OSR_1_9_data[]=					{RF_MODEM_BCR_OSR_1_9};
const unsigned char RF_MODEM_AFC_GEAR_7_data[]=						{RF_MODEM_AFC_GEAR_7};
const unsigned char RF_MODEM_AGC_WINDOW_SIZE_9_data[]=				{RF_MODEM_AGC_WINDOW_SIZE_9};
const unsigned char RF_MODEM_OOK_CNT1_11_data[]=					{RF_MODEM_OOK_CNT1_11};
const unsigned char RF_MODEM_CHFLT_RX1_CHFLT_COE13_7_0_12_data[]=	{RF_MODEM_CHFLT_RX1_CHFLT_COE13_7_0_12};
const unsigned char RF_MODEM_CHFLT_RX1_CHFLT_COE1_7_0_12_data[]=	{RF_MODEM_CHFLT_RX1_CHFLT_COE1_7_0_12};
const unsigned char RF_MODEM_CHFLT_RX2_CHFLT_COE7_7_0_12_data[]=	{RF_MODEM_CHFLT_RX2_CHFLT_COE7_7_0_12};
const unsigned char RF_SYNTH_PFDCP_CPFF_7_data[]=					{RF_SYNTH_PFDCP_CPFF_7};

const unsigned char tx_test_aa_data[14] = {0xaa,0xaa,0xaa,0xaa,0xaa,0xaa,0xaa,0xaa,0xaa,0xaa,0xaa,0xaa,0xaa,0xaa};  
const unsigned char tx_ph_data[14] = {'s','w','w','x',0x41,0x42,0x43,0x44,0x45,0x46,0x47,0x48,0x49,0x6d};  

//Pins

int SDI  = 12
int SDO  = 11
int SCK  = 13
int SS   = 10
 
int GPIO = 4
int SDN  = 7
int LED  = 13

void Setup(){
	
	pinMode(LED, OUTPUT);
	pinMode(SDN, OUTPUT);

	digitalWrite(SDN, HIGH);
	setupRadio();
}

void sendCommand(int tx, in rx, const char* data){
	digitalWrite(SS, LOW);
	char answer;

	for(int i = 0; i < tx; i++){
		byte d = data[i];
		SPI.transfer(d);
	}

	digitalWrite(SS, HIGH);

	delayMicroseconds(20);

	digitalWrite(SS, LOW);

	int reply = 0x00;

	while(reply != 0xFF){
		reply = SPI.transfer(0x44);
		if(reply != 0xFF){
			digitalWrite(SS, HIGH);
			delayMicroseconds(20);
			digitalWrite(SS, LOW);
		}
	}

	digitalWrite(SS, HIGH);
	delay(500);
}

void setupRadio(){
	initSPI();
	setFrequency(RADIO_FREQUENCY);
	setShift(RTTY_SHIFT);
	setPowerLevel(POWER_LEVEL);
	radioInit();
}

void initSPI(){
	SPI.begin();
	SPI.setDataMode(SPI_MODE0);
	SPI.setClockDivider(SPI_CLOCK_DIV2)
}

void setFrequency(unsigned long freq){
	
}

void setShift(){

}

void setPowerLevel(){

}

void radioInit(){
	
	pinMode(GPIO, OUTPUT);
	delay(100);

	digitalWrite(SDN, HIGH);
	delay(600);
	digitalWrite(SDN, LOW);

	//Return Part Info
	const char PART_INFO_COMMAND[] = {0x01};
	sendCommand(1, 9, PART_INFO_COMMAND);

	//Power Up
	sendCommand(7,1,RF_POWER_UP_data)

	//Get Interrupt status
	const char GET_INT_STATUS[] = {0x20, 0x00, 0x00, 0x00};
	sendCommand(4, 9, GET_INT_STATUS)

	//GPIO Config
	sendCommand(7, 6,RF_GPIO_PIN_CFG_data)

}

void startTX(){

}

void stopTX(){

}

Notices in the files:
parts and their libraries:
SparkFun-DigitalIC: Licensing: CC v3.0 Share-Alike You are welcome to use this library for commercial purposes.
